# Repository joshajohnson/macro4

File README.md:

# macro4 - A small macro pad

Status: V0.2 tested and working

Features:
- 2x2 layout with encoder support on top locations
- STM32F072 with Type C connector
- Somewhat cost optimised / JLCSMT optimised design

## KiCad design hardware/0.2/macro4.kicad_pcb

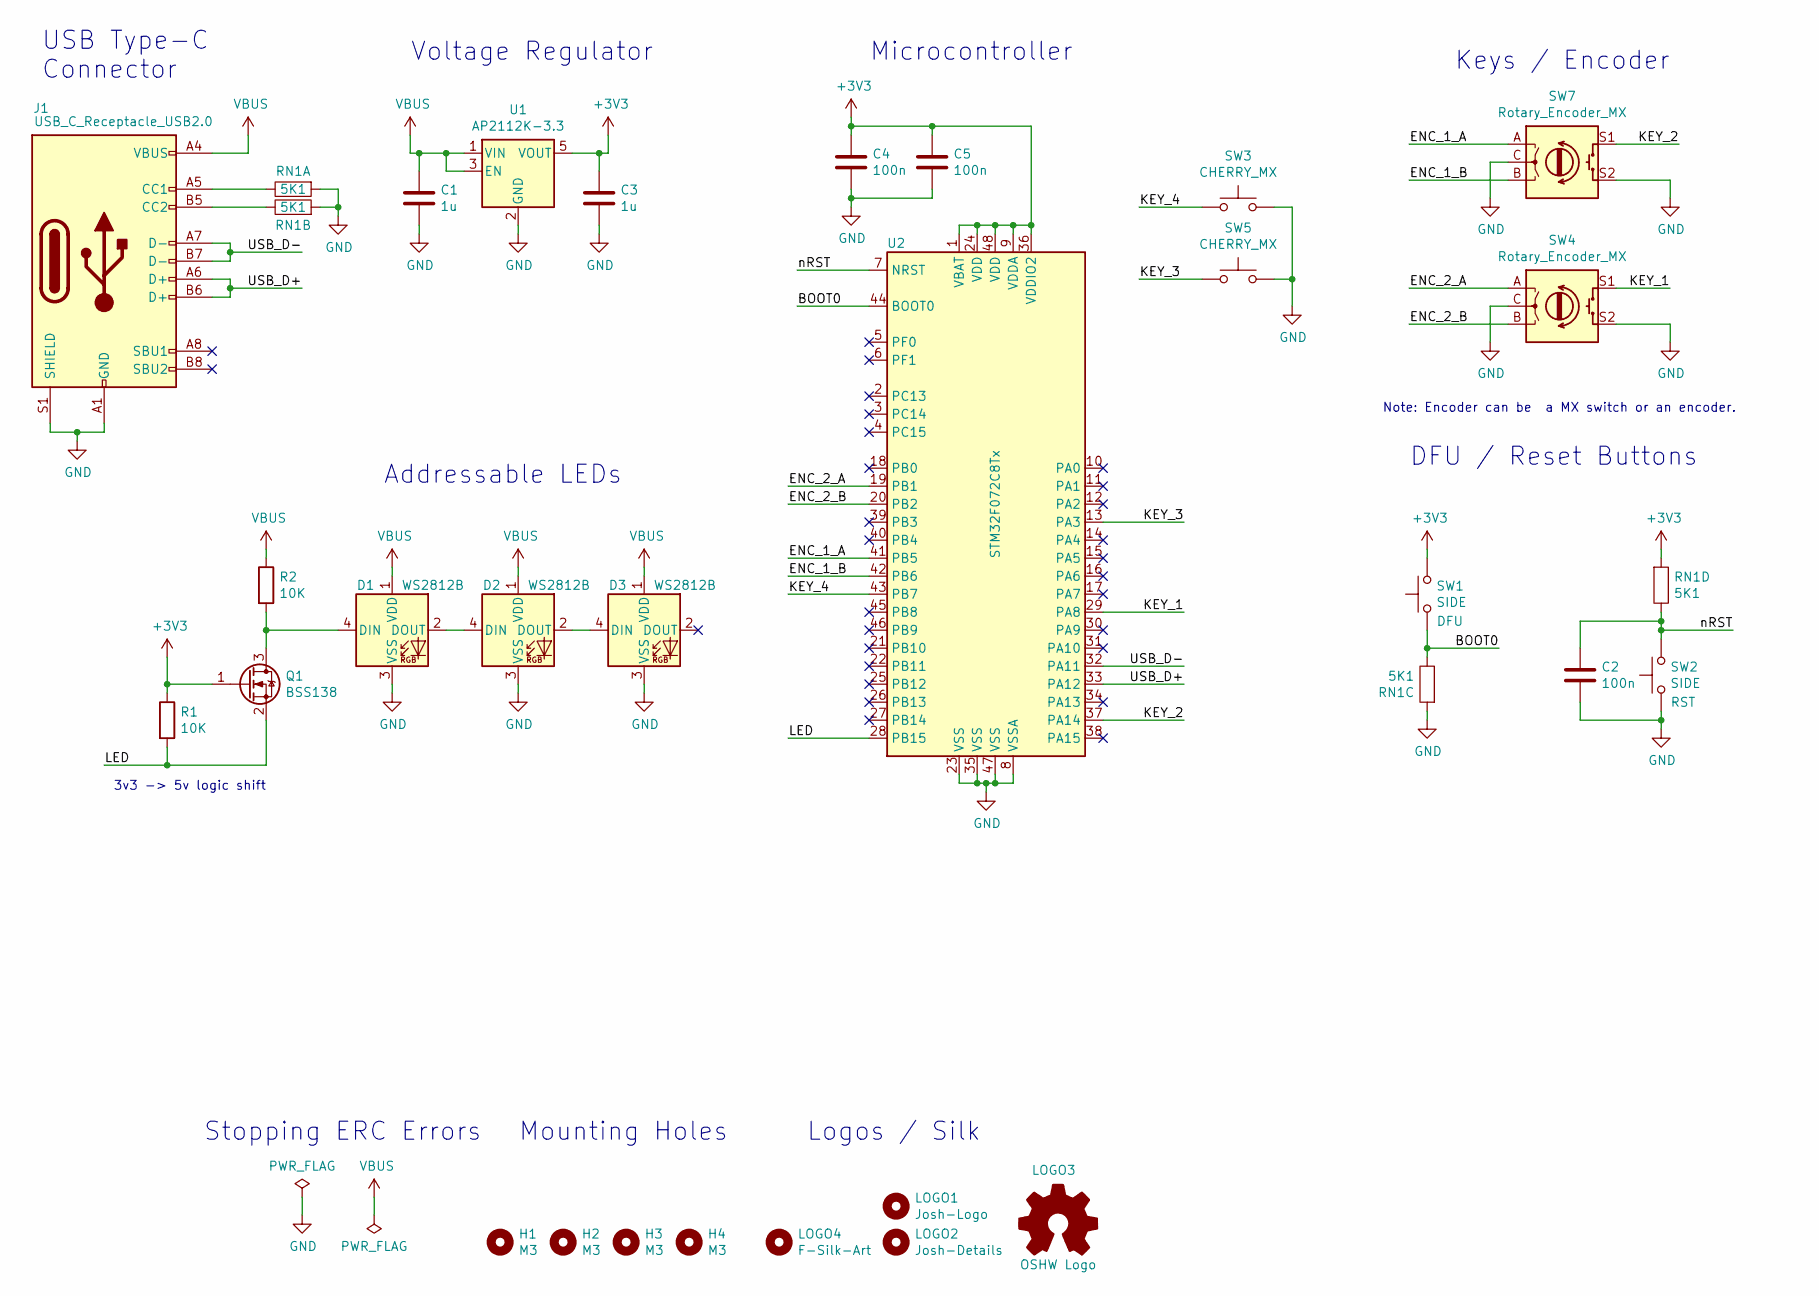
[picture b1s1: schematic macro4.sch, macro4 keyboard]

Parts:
C1, C3: 1u; C_0603_1608Metric; MPN CL10A105MP8NNNC; LCSC C15849
C2, C4, C5: 100n; C_0603_1608Metric; MPN CL10B104KB8NNNC; LCSC C14663
D1, D2, D3: WS2812B; LED_WS2812B_PLCC4_5.0x5.0mm_P3.2mm; MPN WS2812B-B; DigiKey 1528-1104-ND
H1, H2, H3, H4: M3; MountingHole_3.2mm_M3
J1: USB_C_Receptacle_USB2.0; USB_C_U262-161N-4BVC11; MPN U262-161N-4BVC11; LCSC C319148
LOGO1: Josh-Logo; josh-johnson-logo-17x3
LOGO2: Josh-Details; josh-details
LOGO3: OSHW Logo; OSHW_Logo_3.6x3.6_F.Mask
LOGO4: F-Silk-Art; pattern_top
Q1: BSS138; SOT-23; MPN BSS138P,215; LCSC C75547
R1, R2: 10K; R_0603_1608Metric; MPN CR0603-JW-103ELF; DigiKey CR0603-JW-103ELFCT-ND
RN1: 5K1; R_Array_Convex_4x0603; MPN CAY16-512J4LF; LCSC C12028
SW1, SW2: SIDE; Panasonic_EVQPUL_EVQPUC; MPN PTS840GMSMTRLFS; LCSC C221909
SW3, SW5: CHERRY_MX; MX_KEYSWITCH
SW4, SW7: Rotary_Encoder_MX; MX_KEYSWITCH_ENCODER
U1: AP2112K-3.3; SOT-23-5; MPN AP2112K-3.3TRG1; LCSC C51118
U2: STM32F072C8Tx; LQFP-48_7x7mm_P0.5mm; MPN STM32F072C8T6; LCSC C80488

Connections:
+3V3: C3.2, C4.1, C5.1, Q1.1 (G), R1.1, RN1.1, SW1.2, U1.5 (VOUT), U2.1 (VBAT), U2.9 (VDDA), U2.24 (VDD), U2.36 (VDDIO2), U2.48 (VDD)
/BOOT0: RN1.7, SW1.1, U2.44 (BOOT0)
/ENC_1_A: SW7.A, U2.41 (PB5)
/ENC_1_B: SW7.B, U2.42 (PB6)
/ENC_2_A: SW4.A, U2.19 (PB1)
/ENC_2_B: SW4.B, U2.20 (PB2)
/KEY_1: SW7.S1, U2.37 (PA14)
/KEY_2: SW4.S1, U2.29 (PA8)
/KEY_3: SW5.1, U2.13 (PA3)
/KEY_4: SW3.1, U2.43 (PB7)
/LED: Q1.2 (S), R1.2, U2.28 (PB15)
/USB_D+: J1.A6 (D+), J1.B6 (D+), U2.33 (PA12)
/USB_D-: J1.A7 (D-), J1.B7 (D-), U2.32 (PA11)
/nRST: C2.1, RN1.8, SW2.2, U2.7 (NRST)
GND: C1.1, C2.2, C3.1, C4.2, C5.2, D1.3 (VSS), D2.3 (VSS), D3.3 (VSS), J1.A1 (GND), J1.A12 (GND), J1.B1 (GND), J1.B12 (GND), J1.S1 (SHIELD), RN1.2, RN1.3, RN1.4, SW2.1, SW3.2, SW4.C, SW4.S2, SW5.2, SW7.C, SW7.S2, U1.2 (GND), U2.8 (VSSA), U2.23 (VSS), U2.35 (VSS), U2.47 (VSS)
unnamed: D1.2 (DOUT), D2.4 (DIN)
unnamed: D1.4 (DIN), Q1.3 (D), R2.2
unnamed: D2.2 (DOUT), D3.4 (DIN)
unnamed: J1.A5 (CC1), RN1.5
unnamed: J1.B5 (CC2), RN1.6
VBUS: C1.2, D1.1 (VDD), D2.1 (VDD), D3.1 (VDD), J1.A4 (VBUS), J1.A9 (VBUS), J1.B4 (VBUS), J1.B9 (VBUS), R2.1, U1.1 (VIN), U1.3 (EN)

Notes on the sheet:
USB Type-C Connector
Voltage Regulator
Microcontroller
DFU / Reset Buttons
Keys / Encoder
Note: Encoder can be a MX switch or an encoder.
Mounting Holes
Stopping ERC Errors
Addressable LEDs
3v3 -> 5v logic shift
Logos / Silk

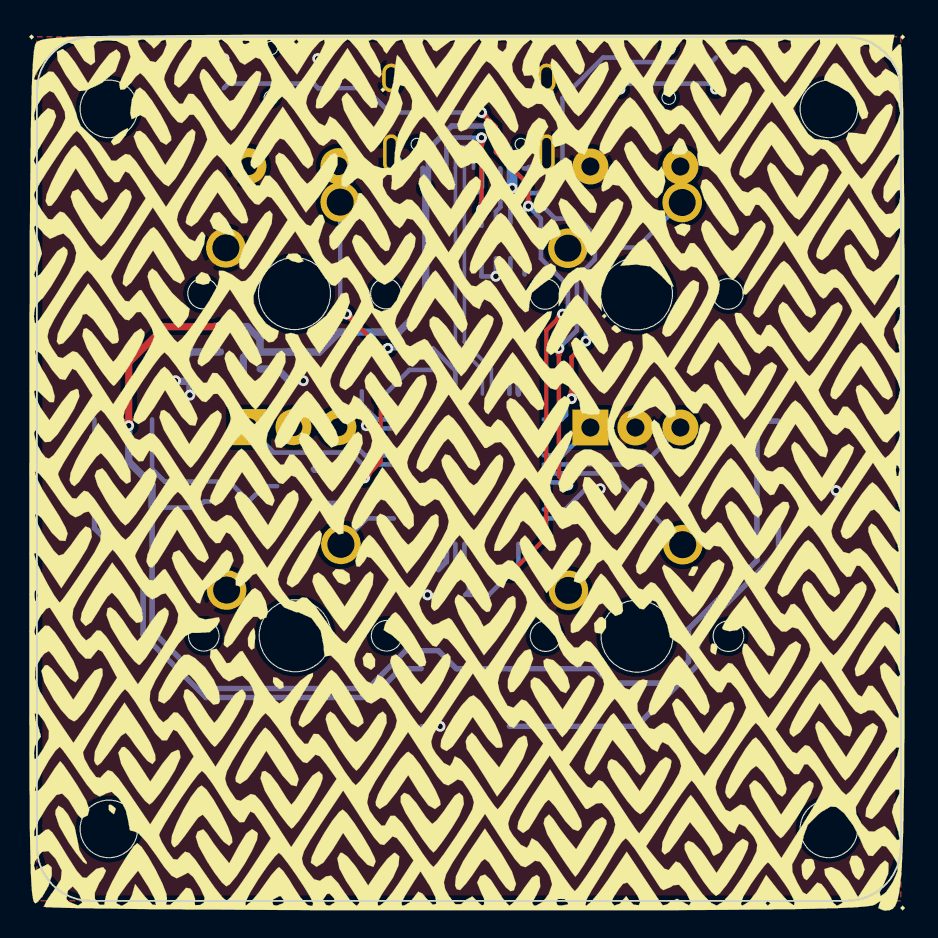
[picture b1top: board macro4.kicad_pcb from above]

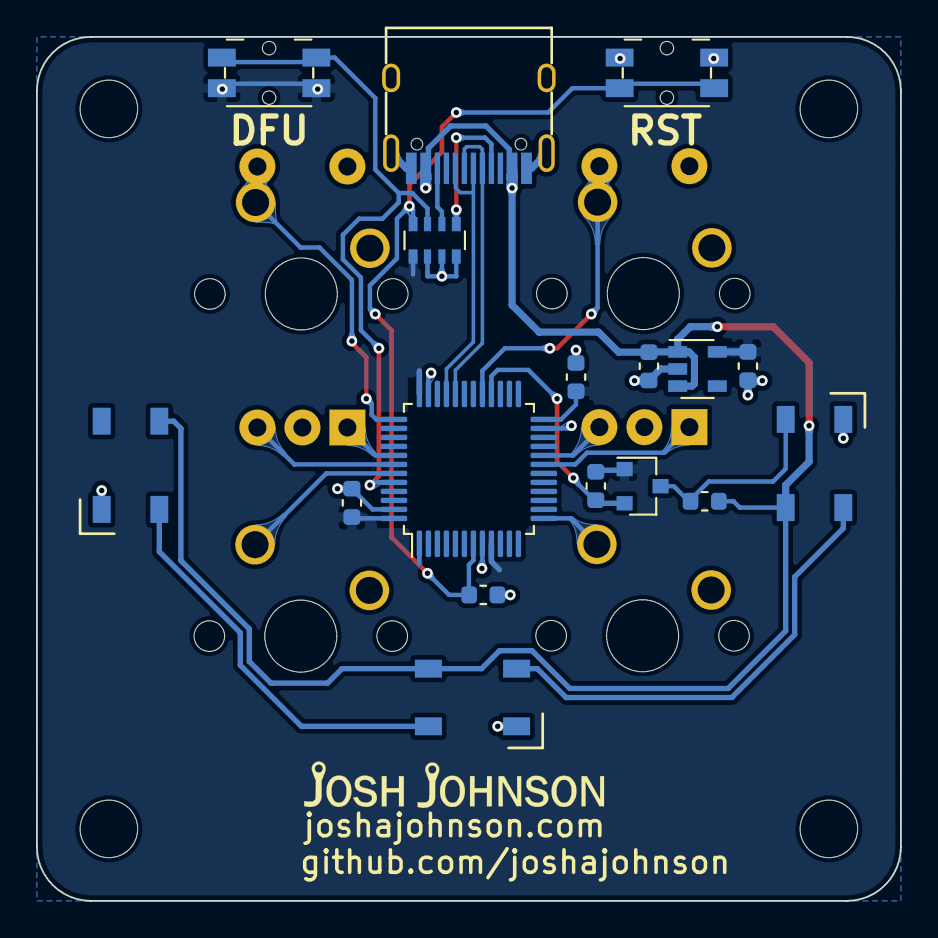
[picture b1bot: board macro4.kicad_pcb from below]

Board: 2 copper layers, 48.0 x 48.0 mm, 29 parts (20 on the bottom side), 21 nets.

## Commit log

2020-01-04 initial layout done
2020-01-07 add RGB and silk to macro4
2020-01-15 change buttons
2020-01-17 update due to breaking lib change
2020-03-28 v0.2
2020-05-23 added second encoder, fixed panelisation script
2020-06-28 fix assembly version bug
